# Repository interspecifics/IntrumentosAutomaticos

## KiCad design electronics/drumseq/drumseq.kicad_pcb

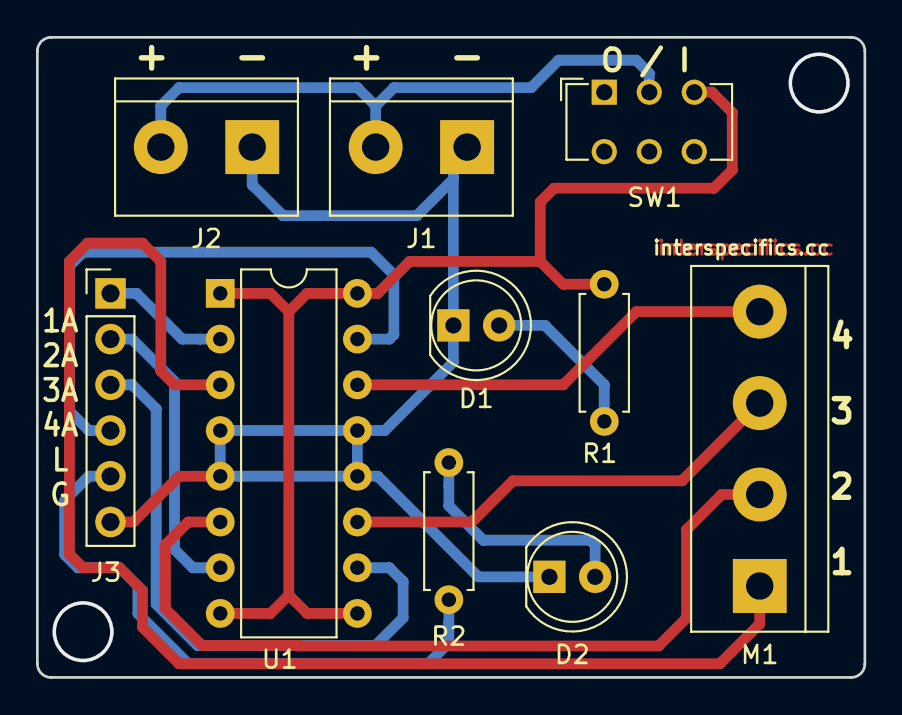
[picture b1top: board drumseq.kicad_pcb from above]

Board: 2 copper layers, 46.0 x 35.6 mm, 10 parts (0 on the bottom side), 14 nets.

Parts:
D1, D2: LED; LED_D5.0mm_FlatTop
J1, J2: POW; TerminalBlock_bornier-2_P5.08mm
J3: Conn_01x06_Male; PinHeader_1x06_P2.54mm_Vertical
M1: Stepper_Motor_bipolar; TerminalBlock_bornier-4_P5.08mm
R1, R2: 330; R_Axial_DIN0207_L6.3mm_D2.5mm_P7.62mm_Horizontal
SW1: SWITCH; SW_CuK_JS202011CQN_DPDT_Straight
U1: L293D; DIP-16_W7.62mm

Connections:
GND: D1.1, D2.1, J1.1, J2.1, J3.6, U1.4, U1.5, U1.12, U1.13
unnamed: D1.2, R1.1
unnamed: D2.2, R2.1
unnamed: J1.2, J2.2, SW1.2
unnamed: J3.1, U1.2
unnamed: J3.2, U1.7
unnamed: J3.3, U1.10
unnamed: J3.4, U1.15
unnamed: J3.5, R2.2
unnamed: M1.1, U1.3
unnamed: M1.2, U1.6
unnamed: M1.3, U1.11
unnamed: M1.4, U1.14
VCC: R1.2, SW1.3, U1.1, U1.8, U1.9, U1.16

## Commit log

2019-05-15 secuenciador y complementos
2019-05-15 electronics
